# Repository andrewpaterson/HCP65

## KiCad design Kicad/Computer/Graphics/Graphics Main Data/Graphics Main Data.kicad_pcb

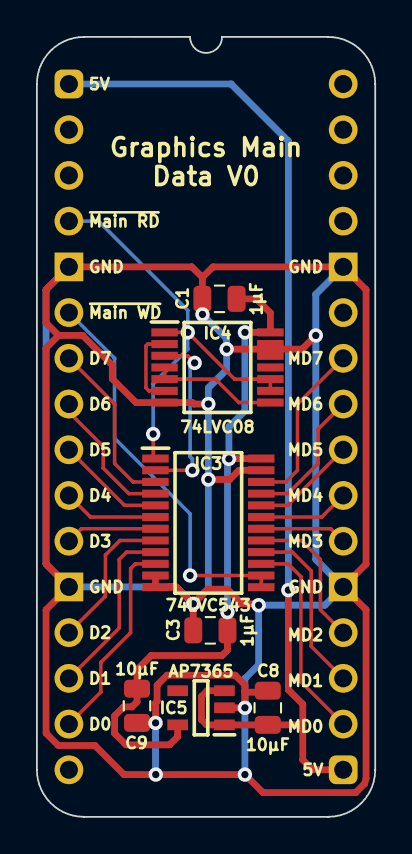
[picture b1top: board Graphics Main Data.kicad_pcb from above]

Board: 2 copper layers, 18.8 x 43.3 mm, 8 parts (0 on the bottom side), 24 nets.

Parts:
C1, C3: 1μF; C_0805
C8, C9: 10µF; C_0805
IC3: SN74LVC543APWR; SOP65P640X120-24N
IC4: 74LVC08APW,112; SOP65P640X110-14N
IC5: AP7365-33WG-7; SOT95P285X130-5N
J5: Board 2x16 W15.24mm; DIP-32_Board_W15.24mm

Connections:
5V: C8.1, IC5.1 (6VIn), IC5.3 (EN), J5.1, J5.17
/3.3V: C1.1, C3.1, C9.1, IC3.24 (3V), IC4.14 (3V), IC5.5 (3.3VOut)
/~Read_{2}: IC4.4 (2A), IC4.5 (2B), IC4.8 (3Y)
/~Read_{3}: IC4.2 (1B), IC4.6 (2Y)
/~Read_{4}: IC3.2 (~OEA), IC4.3 (1Y)
D0: IC3.10 (A8), J5.15
D1: IC3.9 (A7), J5.14
D2: IC3.8 (A6), J5.13
D3: IC3.7 (A5), J5.11
D4: IC3.6 (A4), J5.10
D5: IC3.5 (A3), J5.9
D6: IC3.4 (A2), J5.8
D7: IC3.3 (A1), J5.7
GND: C1.2, C3.2, C8.2, C9.2, IC3.11 (~CEAB), IC3.12 (GND), IC3.23 (~CEBA), IC4.7 (GND), IC4.12 (4A), IC4.13 (4B), IC5.2 (GND), J5.5, J5.12, J5.21, J5.28
MD0: IC3.15 (B8), J5.18
MD1: IC3.16 (B7), J5.19
MD2: IC3.17 (B6), J5.20
MD3: IC3.18 (B5), J5.22
MD4: IC3.19 (B4), J5.23
MD5: IC3.20 (B3), J5.24
MD6: IC3.21 (B2), J5.25
MD7: IC3.22 (B1), J5.26
~Main Read: IC3.1 (~LEB), IC4.1 (1A), IC4.9 (3A), IC4.10 (3B), J5.4
~Main Write: IC3.13 (~OEB), IC3.14 (~LEA), J5.6

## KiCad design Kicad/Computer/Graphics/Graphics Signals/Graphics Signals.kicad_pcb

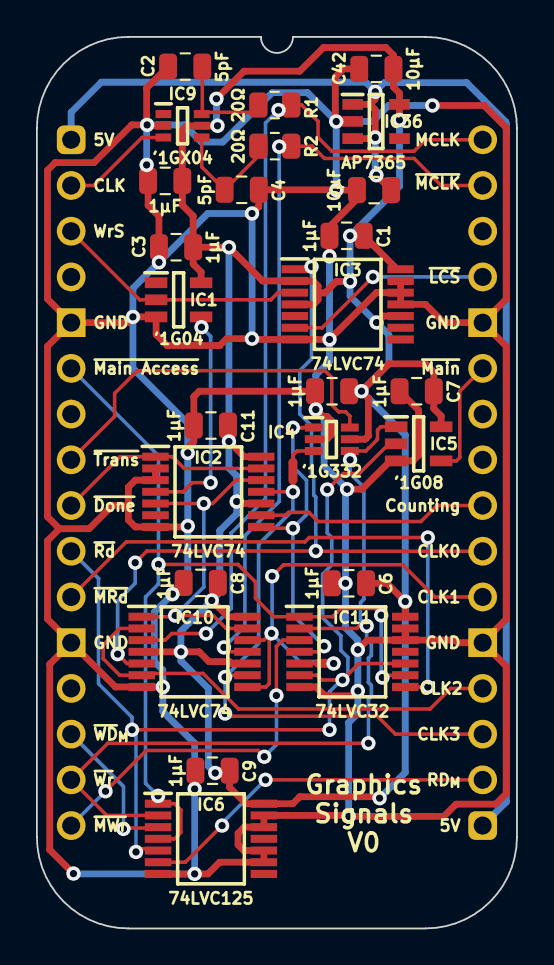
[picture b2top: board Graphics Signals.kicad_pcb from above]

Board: 2 copper layers, 26.7 x 49.5 mm, 28 parts (0 on the bottom side), 30 nets.

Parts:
C1, C3, C5, C6, C7, C8, C9, C10, C11: 1μF; C_0805
C2, C4: 5pF; C_0805
C41, C42: 10μF; C_0805
IC1: 74LVC1G04GV,125; SOT95P275X110-5N
IC2, IC3, IC10: 74LVC74APW,118; SOP65P640X110-14N
IC4: SN74LVC1G332DCKR; SOT65P210X110-6N
IC5: 74LVC1G08GV,125; SOT95P275X110-5N
IC6: 74LVC125APW-Q100J; SOP65P640X110-14N
IC9: 74LVC1GX04GW,125; SOP65P210X110-6N
IC11: 74LVC32APW,118; SOP65P640X110-14N
IC36: AP7365-33WG-7; SOT95P285X130-5N
J7: Board 2x16 W22.86mm; DIP-32_Board_W22.86mm
NT1, NT2: NetTie_2; NetTie-2_SMD_Pad0.5mm
R1, R2: 20Ω; R_0805

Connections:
5V: C41.1, IC36.1 (6VIn), IC36.3 (EN), J7.1, J7.17
/3.3V: C1.2, C3.1, C5.2, C6.2, C7.2, C8.2, C9.2, C10.2, C11.2, C42.1, IC1.5 (3V), IC2.10 (~2SD), IC2.14 (3V), IC3.2 (1D), IC3.4 (~1SD), IC3.10 (~2SD), IC3.14 (3V), IC4.5 (3V), IC5.5 (3V), IC6.14 (3V), IC9.5 (3V), IC10.4 (~1SD), IC10.10 (~2SD), IC10.14 (3V), IC11.14 (3V), IC36.5 (3.3VOut)
/Running: IC2.5 (1Q), IC2.12 (2D), IC10.1 (~1RD), IC10.13 (~2RD)
/~Counting: IC2.8 (~2Q), IC4.1 (A), IC11.4 (2A)
/~Write Start: IC1.4 (Y), IC2.4 (~1SD)
/~Write w/o Tansparency: IC4.3 (B), NT1.2
CLK0: IC3.1 (~1RD), IC10.5 (1Q), J7.23
CLK1: IC10.8 (~2Q), IC10.12 (2D), J7.22, NT2.1
CLK2: IC10.2 (1D), IC10.6 (~1Q), J7.20
CLK3: IC2.11 (2CP), IC10.9 (2Q), J7.19, NT1.1
Counting: IC2.9 (2Q), J7.24
GND: C1.1, C2.2, C3.2, C4.2, C5.1, C6.1, C7.1, C8.1, C9.1, C10.1, C11.1, C41.2, C42.2, IC1.3 (GND), IC2.2 (1D), IC2.3 (1CP), IC2.7 (GND), IC3.7 (GND), IC3.11 (2CP), IC3.12 (2D), IC3.13 (~2RD), IC4.2 (GND), IC5.3 (GND), IC6.7 (GND), IC6.9 (3A), IC6.10 (~3OE), IC6.12 (4A), IC6.13 (~4OE), IC9.2 (GND), IC10.7 (GND), IC11.7 (GND), IC11.12 (4A), IC11.13 (4B), IC36.2 (GND), J7.5, J7.12, J7.21, J7.28
MCLK: IC10.3 (1CP), J7.32, R1.2
Main CLK: IC9.3 (X1), J7.2
unnamed: C2.1, IC9.6 (Y), R1.1
unnamed: C4.1, IC9.4 (~Y), R2.1
unnamed: IC11.5 (2B), NT2.2
Transparent: IC4.6 (C), J7.8
Write Start: IC1.2 (A), IC3.3 (1CP), J7.3
~Done: IC2.1 (~1RD), IC2.13 (~2RD), J7.9
~Load Count Start: IC3.6 (~1Q), J7.29
~MCLK: IC10.11 (2CP), J7.31, R2.2
~Main Access: IC6.1 (~1OE), IC6.4 (~2OE), IC11.1 (1A), IC11.9 (3A), J7.6
~Main RD: IC6.6 (2Y), J7.18
~Main Read: IC11.8 (3Y), J7.11
~Main WD: IC6.3 (1Y), J7.14
~Main Write: IC11.3 (1Y), J7.16
~Main: IC5.4 (Y), J7.27
~Read: IC5.2 (A), IC6.5 (2A), IC11.6 (2Y), IC11.10 (3B), J7.10
~Write: IC4.4 (Y), IC5.1 (B), IC6.2 (1A), IC11.2 (1B), J7.15

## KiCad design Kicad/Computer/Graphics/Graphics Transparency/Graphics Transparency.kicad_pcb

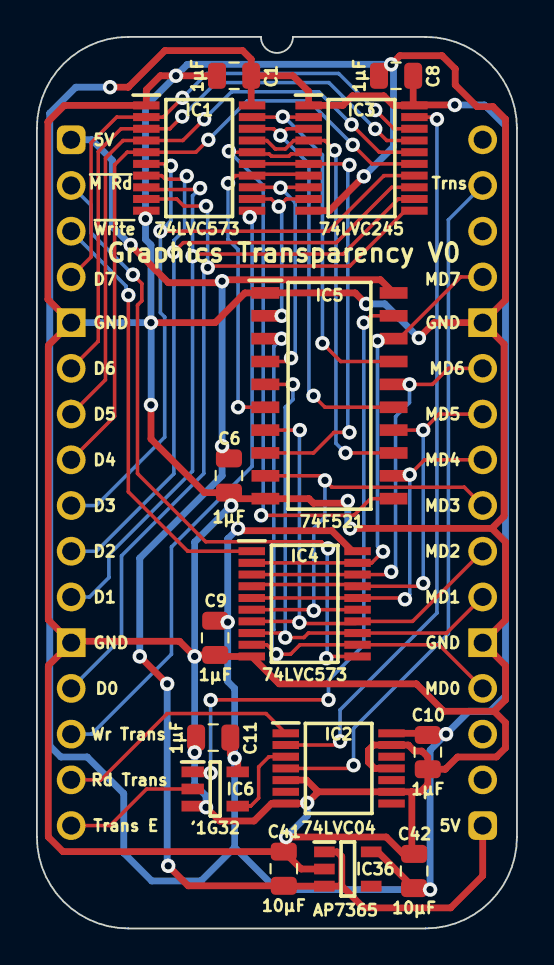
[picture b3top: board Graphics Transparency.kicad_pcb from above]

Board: 2 copper layers, 26.7 x 49.5 mm, 16 parts (0 on the bottom side), 36 nets.

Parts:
C1, C6, C8, C9, C10, C11: 1μF; C_0805
C41, C42: 10μF; C_0805
IC1, IC4: 74LVC573APW,118; SOP65P640X110-20N
IC2: 74LVC04APW,118; SOP65P640X110-14N
IC3: 74LVC245AT20; SOP65P640X120-20N
IC5: SN74F521NSR; SOIC127P780X200-20N
IC6: 74LVC1G32GV,125; SOT95P275X110-5N
IC36: AP7365-33WG-7; SOT95P285X130-5N
J7: Board 2x16 W22.86mm; DIP-32_Board_W22.86mm

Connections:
5V: C6.2, C41.1, IC5.20 (5V), IC36.1 (6VIn), IC36.3 (EN), J7.1, J7.17
/3.3V: C1.2, C8.2, C9.2, C10.2, C11.2, C42.1, IC1.20 (3V), IC2.14 (3V), IC3.1 (DIR), IC3.20 (3V), IC4.20 (3V), IC6.5 (3V), IC36.5 (3.3VOut)
/T0: IC1.12 (Q7), IC3.9 (A7), IC5.2 (P0)
/T1: IC1.13 (Q6), IC3.8 (A6), IC5.4 (P1)
/T2: IC1.14 (Q5), IC3.7 (A5), IC5.6 (P2)
/T3: IC1.15 (Q4), IC3.6 (A4), IC5.8 (P3)
/T4: IC1.16 (Q3), IC3.5 (A3), IC5.11 (P4)
/T5: IC1.17 (Q2), IC3.4 (A2), IC5.13 (P5)
/T6: IC1.18 (Q1), IC3.3 (A1), IC5.15 (P6)
/T7: IC1.19 (Q0), IC3.2 (A0), IC5.17 (P7)
/~Read Transparent Colour: IC2.2 (1Y), IC3.19 (~OE)
/~Transparent: IC2.3 (2A), IC6.4 (Y)
D0: IC1.9 (D7), IC3.11 (B7), J7.13
D1: IC1.8 (D6), IC3.12 (B6), J7.11
D2: IC1.7 (D5), IC3.13 (B5), J7.10
D3: IC1.6 (D4), IC3.14 (B4), J7.9
D4: IC1.5 (D3), IC3.15 (B3), J7.8
D5: IC1.4 (D2), IC3.16 (B2), J7.7
D6: IC1.3 (D1), IC3.17 (B1), J7.6
D7: IC1.2 (D0), IC3.18 (B0), J7.4
GND: C1.1, C6.1, C8.1, C9.1, C10.1, C11.1, C41.2, C42.2, IC1.1 (~OE), IC1.10 (GND), IC2.5 (3A), IC2.7 (GND), IC2.9 (4A), IC2.11 (5A), IC2.13 (6A), IC3.10 (GND), IC4.10 (GND), IC5.1 (~OE), IC5.10 (GND), IC6.3 (GND), IC36.2 (GND), J7.5, J7.12, J7.21, J7.28
MD0: IC4.9 (D7), IC4.12 (Q7), IC5.3 (Q0), J7.20
MD1: IC4.8 (D6), IC4.13 (Q6), IC5.5 (Q1), J7.22
MD2: IC4.7 (D5), IC4.14 (Q5), IC5.7 (Q2), J7.23
MD3: IC4.6 (D4), IC4.15 (Q4), IC5.9 (Q3), J7.24
MD4: IC4.5 (D3), IC4.16 (Q3), IC5.12 (Q4), J7.25
MD5: IC4.4 (D2), IC4.17 (Q2), IC5.14 (Q5), J7.26
MD6: IC4.3 (D1), IC4.18 (Q1), IC5.16 (Q6), J7.27
MD7: IC4.2 (D0), IC4.19 (Q0), IC5.18 (Q7), J7.29
unnamed: IC5.19 (~P=Q), IC6.1 (B)
Read Transparent Colour: IC2.1 (1A), J7.15
Transparency Enable: IC6.2 (A), J7.16
Transparent: IC2.4 (2Y), J7.31
Write Transparent Colour: IC1.11 (LE), J7.14
~Main Read: IC4.11 (LE), J7.2
~Write: IC4.1 (~OE), J7.3

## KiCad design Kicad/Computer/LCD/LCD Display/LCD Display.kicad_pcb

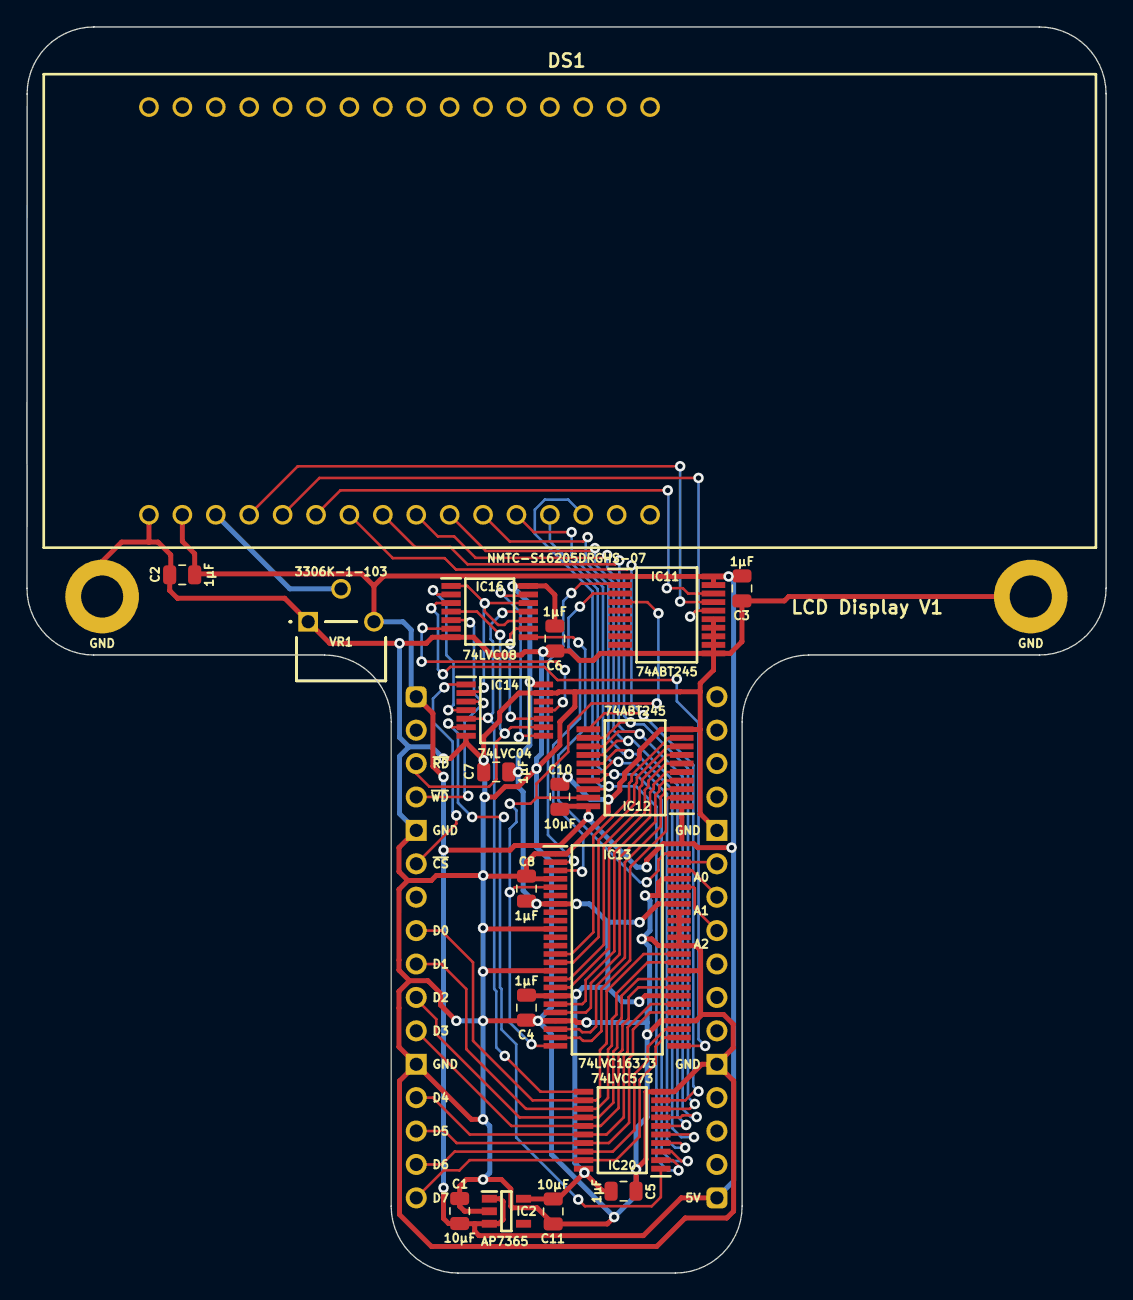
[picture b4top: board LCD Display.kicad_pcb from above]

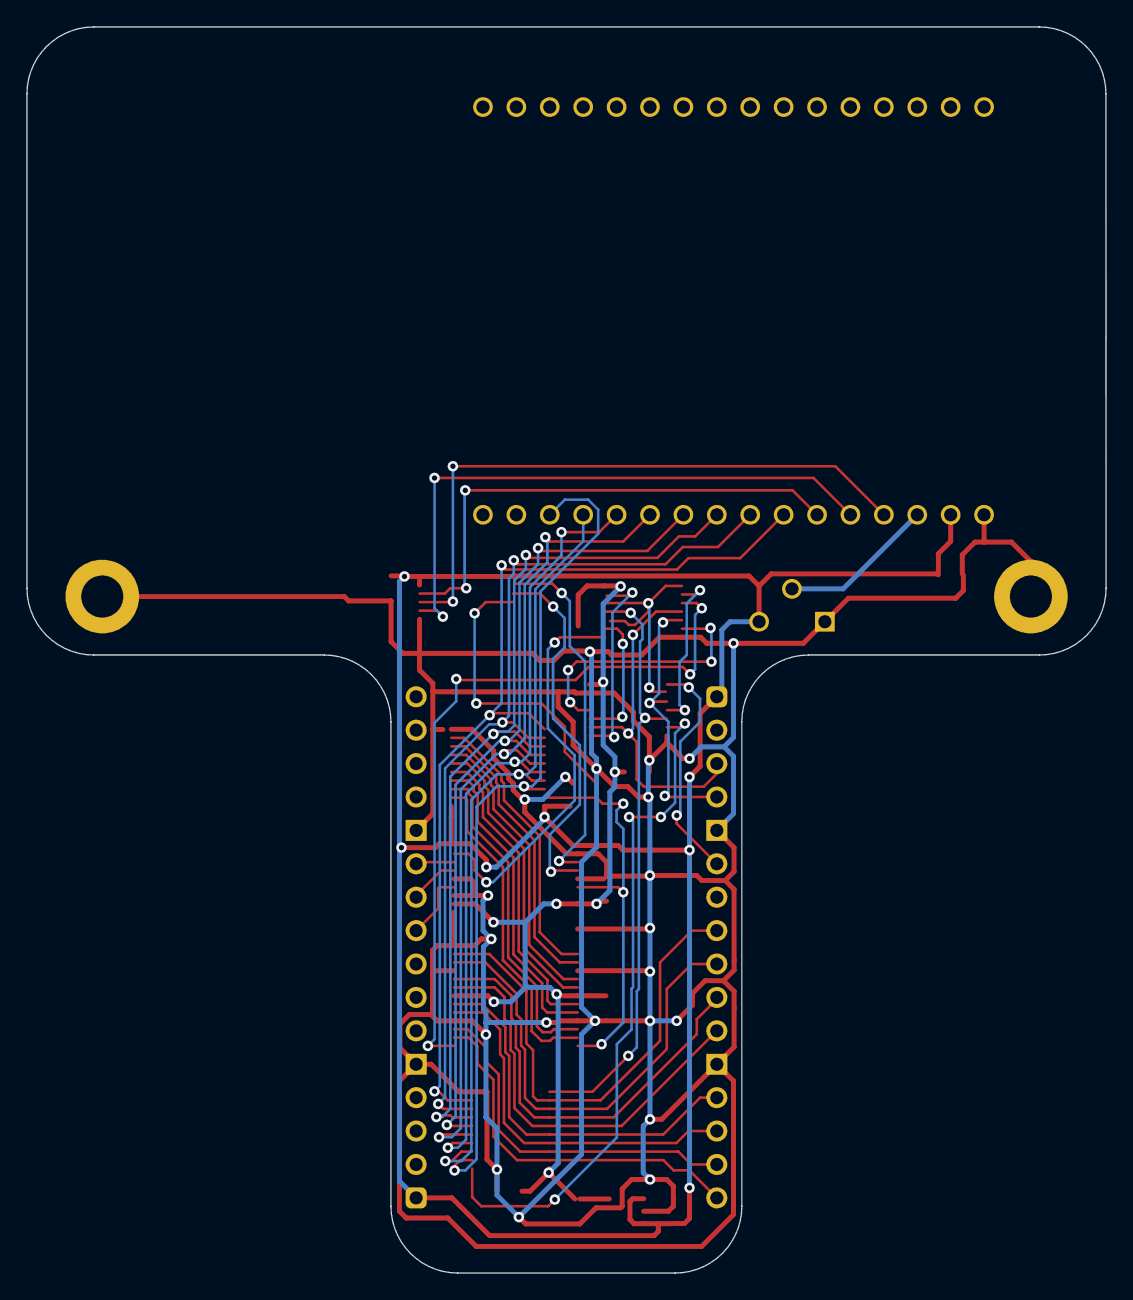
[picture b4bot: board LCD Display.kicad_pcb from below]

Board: 2 copper layers, 82.0 x 94.7 mm, 24 parts (2 on the bottom side), 49 nets.

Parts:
C1, C10, C11: 10μF; C_0805
C2, C3, C4, C5, C6, C7, C8: 1μF; C_0805
DS1: NMTC-S16205DRGHS-07; NMTCS16205DRGHS07_1
H1, H2: MountingHole_Pad; HCP65_MountingHole_M3_
IC2: AP7365-33WG-7; SOT95P285X130-5N
IC11, IC12: SN74ABT245BDBR; SOP65P780X200-20N
IC13: 74LVC16373ADL,118; SOP64P1025X280-48N
IC14: 74LVC04APW,118; SOP65P640X110-14N
IC16: 74LVC08APW,112; SOP65P640X110-14N
IC20: 74LVC573APW,118; SOP65P640X110-20N
J1: Board 2x16 W22.86mm; DIP-32_Board_W22.86mm_Nak
J2, J3: Pin_Header_01x16; PinHeader_1x16_P2.54mm_Vertical
VR1: 3306K-1-103; 3306K1103

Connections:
5V: C1.1, C2.1, C3.1, C10.1, DS1.2 (5V), IC2.1 (6VIn), IC2.3 (EN), IC11.1 (DIR), IC11.19 (~OE), IC11.20 (5V), IC12.1 (DIR), IC12.20 (5V), J1.1, J1.17, VR1.3 (VIN)
/3.3V: C4.1, C5.1, C6.1, C7.1, C8.1, C11.1, IC2.5 (3.3VOut), IC13.7 (3V), IC13.18 (3V), IC13.31 (3V), IC13.42 (3V), IC14.14 (3V), IC16.14 (3V), IC20.20 (3V)
/(RD+WD)·CS: IC13.48 (1LE), IC16.8 (3Y)
/CS: IC14.2 (1Y), IC16.1 (1A), IC16.10 (3B), IC16.12 (4A)
/D0_{Latch}: IC12.9 (A7), IC13.13 (2Q0)
/D1_{Latch}: IC12.8 (A6), IC13.14 (2Q1)
/D2_{Latch}: IC12.7 (A5), IC13.16 (2Q2)
/D3_{Latch}: IC12.6 (A4), IC13.17 (2Q3)
/D4_{Latch}: IC12.5 (A3), IC13.19 (2Q4)
/D5_{Latch}: IC12.4 (A2), IC13.20 (2Q5)
/D6_{Latch}: IC12.3 (A1), IC13.22 (2Q6)
/D7_{Latch}: IC12.2 (A0), IC13.23 (2Q7)
/DB0: DS1.7 (DB0), IC12.11 (B7), IC20.9 (D7)
/DB1: DS1.8 (DB1), IC12.12 (B6), IC20.8 (D6)
/DB2: DS1.9 (DB2), IC12.13 (B5), IC20.7 (D5)
/DB3: DS1.10 (DB3), IC12.14 (B4), IC20.6 (D4)
/DB4: DS1.11 (DB4), IC12.15 (B3), IC20.5 (D3)
/DB5: DS1.12 (DB5), IC12.16 (B2), IC20.4 (D2)
/DB6: DS1.13 (DB6), IC12.17 (B1), IC20.3 (D1)
/DB7: DS1.14 (DB7), IC12.18 (B0), IC20.2 (D0)
/E: DS1.6 (E), IC11.18 (B0)
/E_{Latch}: IC11.2 (A0), IC13.2 (1Q0)
/RD: IC14.8 (4Y), IC16.13 (4B)
/RD+WD: IC14.10 (5Y), IC16.9 (3A)
/RD·CS: IC14.5 (3A), IC16.11 (4Y), IC20.11 (LE)
/RS: DS1.4 (RS), IC11.17 (B1)
/RS_{Latch}: IC11.3 (A1), IC13.3 (1Q1)
/R~W: DS1.5 (R/~W), IC11.16 (B2)
/R~W_{Latch}: IC11.4 (A2), IC12.19 (~OE), IC13.5 (1Q2), IC13.24 (2~OE)
/V_{0}: DS1.3 (V_{O}), VR1.2 (VOUT)
/WD: IC14.4 (2Y), IC16.2 (1B)
/WD·CS: IC13.25 (2LE), IC16.3 (1Y)
/~RD+~CS: IC14.6 (3Y), IC20.1 (~OE)
/~RD·~WD: IC14.11 (5A), IC16.6 (2Y)
A0: IC13.47 (1D0), J1.27
A1: IC13.46 (1D1), J1.26
A2: IC13.44 (1D2), J1.25
D0: IC13.36 (2D0), IC20.12 (Q7), J1.8
D1: IC13.35 (2D1), IC20.13 (Q6), J1.9
D2: IC13.33 (2D2), IC20.14 (Q5), J1.10
D3: IC13.32 (2D3), IC20.15 (Q4), J1.11
D4: IC13.30 (2D4), IC20.16 (Q3), J1.13
D5: IC13.29 (2D5), IC20.17 (Q2), J1.14
D6: IC13.27 (2D6), IC20.18 (Q1), J1.15
D7: IC13.26 (2D7), IC20.19 (Q0), J1.16
Device ~CS: IC14.1 (1A), J1.6
GND: C1.2, C2.2, C3.2, C4.2, C5.2, C6.2, C7.2, C8.2, C10.2, C11.2, DS1.1 (GND), H1.1 (GND), H2.1 (GND), IC2.2 (GND), IC11.10 (GND), IC11.11 (B7), IC11.12 (B6), IC11.13 (B5), IC11.14 (B4), IC11.15 (B3), IC12.10 (GND), IC13.1 (1~OE), IC13.4 (GND), IC13.10 (GND), IC13.15 (GND), IC13.21 (GND), IC13.28 (GND), IC13.34 (GND), IC13.37 (1D7), IC13.38 (1D6), IC13.39 (GND), IC13.40 (1D5), IC13.41 (1D4), IC13.43 (1D3), IC13.45 (GND), IC14.7 (GND), IC14.13 (6A), IC16.7 (GND), IC20.10 (GND), J1.5, J1.12, J1.21, J1.28, VR1.1 (GND)
~RD: IC14.9 (4A), IC16.4 (2A), J1.3
~WD: IC14.3 (2A), IC16.5 (2B), J1.4

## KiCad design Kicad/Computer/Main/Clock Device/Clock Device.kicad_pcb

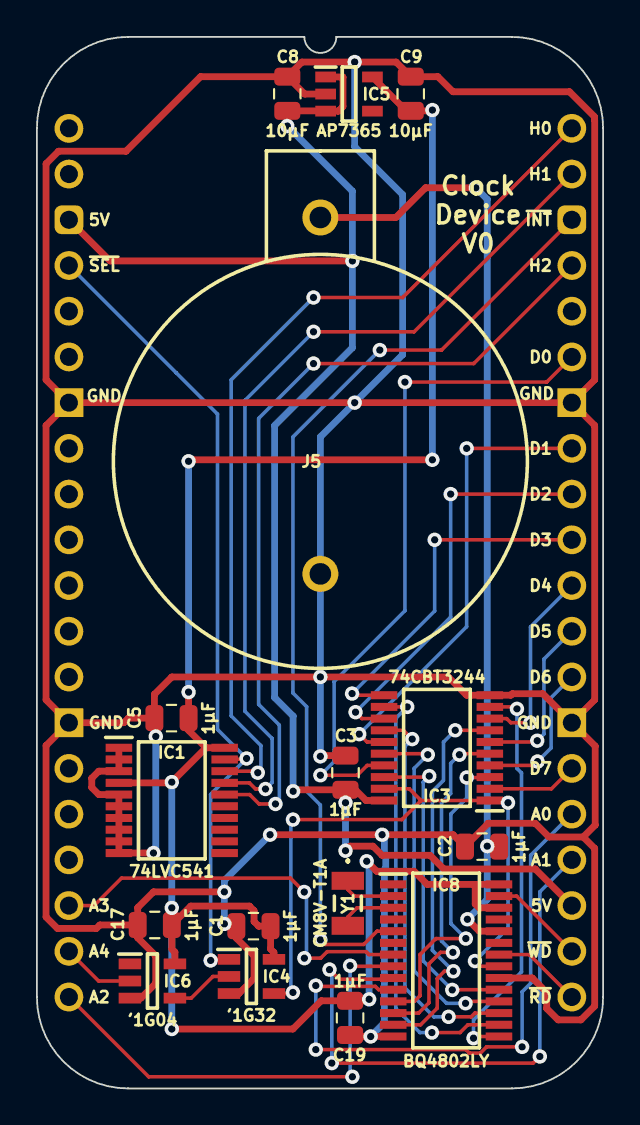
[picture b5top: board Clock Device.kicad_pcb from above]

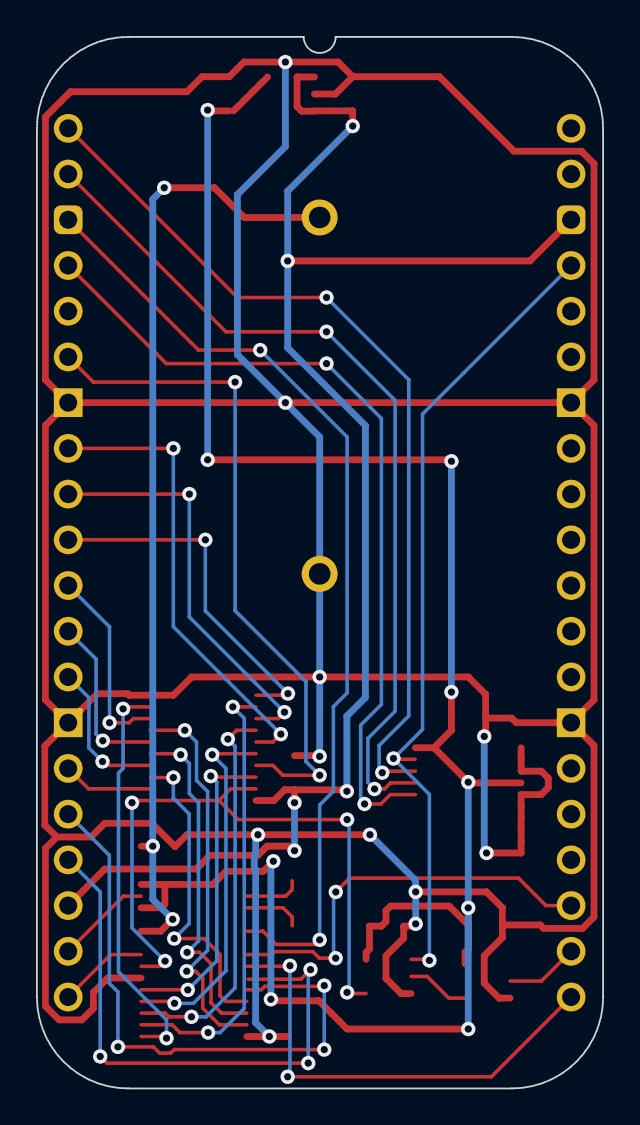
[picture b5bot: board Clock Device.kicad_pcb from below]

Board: 2 copper layers, 31.5 x 58.4 mm, 20 parts (2 on the bottom side), 36 nets.

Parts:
C1, C2, C3, C5, C17, C19: 1μF; C_0805
C8, C9: 10µF; C_0805
IC1: 74LVC541APW,118; SOP65P640X110-20N
IC3: SN74CBT3244CPWR; SOP65P640X120-20N
IC4: 74LVC1G32GV,125; SOT95P275X110-5N
IC5: AP7365-33WG-7; SOT95P285X130-5N
IC6: 74LVC1G04GV,125; SOT95P275X110-5N
IC8: BQ4802LYPWR; SOP65P640X120-28N
J1, J2: Conn_01x20; SIP_20_Pins
J3, J4: Pin_Header_01x20; PinHeader_1x20_P2.54mm_Vertical
J5: 237-8270
Y1: 32.768KHz; SC32S7PF20PPM

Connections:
5V: C3.1, C8.1, IC3.20 (5V), IC5.1 (6VIn), IC5.3 (EN), J1.3, J2.18
/3.3V: C1.1, C5.1, C9.1, C17.1, C19.1, IC1.4 (A2), IC1.20 (3V), IC4.5 (3V), IC5.5 (3.3VOut), IC6.5 (3V), IC8.26 (~CE_{IN}), IC8.28 (3V)
/3V Bat: C2.1, IC8.24 (BC), J5.1 (+)
/DQ0: IC3.3 (2B4), IC8.11 (DQ0)
/DQ1: IC3.5 (2B3), IC8.12 (DQ1)
/DQ2: IC3.7 (2B2), IC8.13 (DQ2)
/DQ3: IC3.9 (2B1), IC8.15 (DQ3)
/DQ4: IC3.12 (1B4), IC8.16 (DQ4)
/DQ5: IC3.14 (1B3), IC8.17 (DQ5)
/DQ6: IC3.16 (1B2), IC8.18 (DQ6)
/DQ7: IC3.18 (1B1), IC8.19 (DQ7)
/X1: IC8.2 (X1), Y1.1
/X2: IC8.3 (X2), Y1.2
/~A4: IC4.2 (A), IC6.4 (Y)
/~CS: IC3.1 (1~OE), IC3.19 (2~OE), IC4.4 (Y), IC8.21 (~CS)
A0: IC8.10 (A0), J2.16
A1: IC8.9 (A1), J2.17
A2: IC8.8 (A2), J1.20
A3: IC8.7 (A3), J1.18
A4: IC6.2 (A), J1.19
D0: IC3.17 (2A4), J2.6
D1: IC3.15 (2A3), J2.8
D2: IC3.13 (2A2), J2.9
D3: IC3.11 (2A1), J2.10
D4: IC3.8 (1A4), J2.11
D5: IC3.6 (1A3), J2.12
D6: IC3.4 (1A2), J2.13
D7: IC3.2 (1A1), J2.15
GND: C1.2, C2.2, C3.2, C5.2, C8.2, C9.2, C17.2, C19.2, IC1.1 (~OE1), IC1.2 (A0), IC1.3 (A1), IC1.5 (A3), IC1.6 (A4), IC1.7 (A5), IC1.8 (A6), IC1.9 (A7), IC1.10 (GND), IC3.10 (GND), IC4.3 (GND), IC5.2 (GND), IC6.3 (GND), IC8.14 (GND), IC8.20 (GND), J1.7, J1.14, J2.7, J2.14, J5.2 (-)
H0: IC1.18 (Y0), J2.1
H1: IC1.17 (Y1), J2.2
H2: IC1.16 (Y2), J2.4
~INT: IC8.5 (~INT), J2.3
~RD: IC8.22 (~OE), J2.20
~Select: IC1.19 (~OE2), IC4.1 (B), J1.4
~WD: IC8.27 (~WE), J2.19

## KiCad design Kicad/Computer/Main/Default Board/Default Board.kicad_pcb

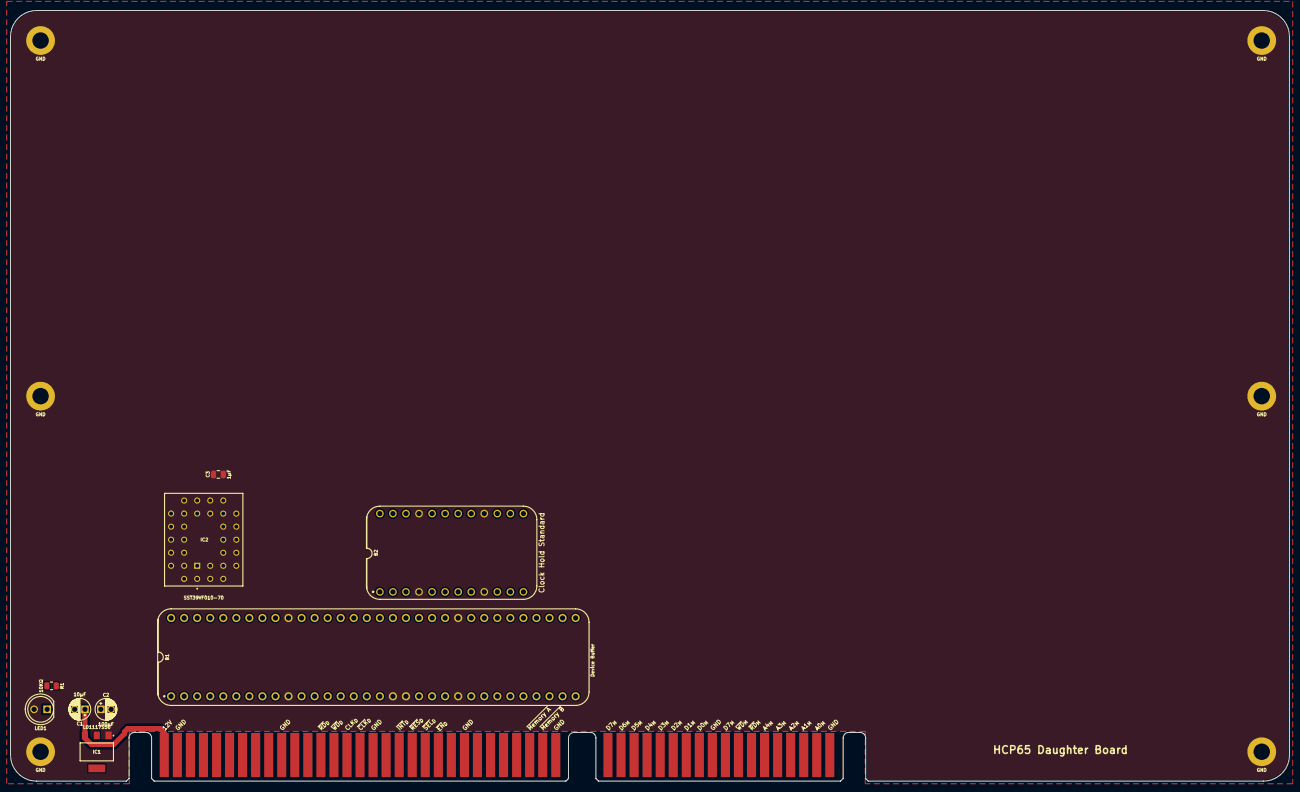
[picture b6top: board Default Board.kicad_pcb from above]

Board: 2 copper layers, 248.9 x 150.0 mm, 16 parts (0 on the bottom side), 66 nets.

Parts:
B1: Device Buffer; HCP65_Device_Buffer
B2: Clock Hold Standard; HCP65_Clock_Hold_Standard
C1: 10μF; CP_Radial_D4.0mm_P2.00mm
C2: 100μF; CP_Radial_D4.0mm_P2.00mm
C3: 1μF; C_0805
H1, H2, H8, H9, H16, H19: MountingHole_Pad; HCP65_MountingHole_M3_
IC1: LD1117S50C; LD1117S33C
IC2: SST39VF010-70-4I-NHE; 5408803224008
J5: 395-098-520-350; 98pin Edge Connector
LED1: Red; LED_D5.0mm
R1: 10KΩ; R_0805

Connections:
/3.3V: B2.6 (H2_{REG}), B2.7 (H1_{REG}), B2.8 (H0_{REG}), B2.24 (3.3V), C3.1, IC2.32 (3V)
/5V: B1.3 (5V), B1.35 (5V), B2.1 (5V), B2.13 (5V), C2.1, IC1.2 (5.0VOut), IC1.4 (5.0VOut), R1.2
/12V: C1.1, IC1.3 (15VIn), J5.B1
/A0: B1.64 (A0), IC2.12 (A0)
/A0_{D}: B1.1 (A0_{IN}), J5.A4
/A1: B1.63 (A1), IC2.11 (A1)
/A1_{D}: B1.2 (A1_{IN}), J5.A5
/A2: B1.62 (A2), IC2.10 (A2)
/A2_{D}: B1.4 (A2_{IN}), J5.A6
/A3: B1.61 (A3), IC2.9 (A3)
/A3_{D}: B1.5 (A3_{IN}), J5.A7
/A4: B1.60 (A4), IC2.8 (A4)
/A4_{D}: B1.6 (A4_{IN}), J5.A8
/A5: B1.59 (A5), IC2.7 (A5)
/A5_{D}: B1.7 (A5_{IN}), J5.A9
/A6: B1.58 (A6), IC2.6 (A6)
/A6_{D}: B1.8 (A6_{IN}), J5.A10
/A7: B1.57 (A7), IC2.5 (A7)
/A7_{D}: B1.9 (A7_{IN}), J5.A11
/A8: B1.56 (A8), IC2.27 (A8)
/A8_{D}: B1.11 (A8_{IN}), J5.A12
/A9: B1.54 (A9), IC2.26 (A9)
/A9_{D}: B1.12 (A9_{IN}), J5.A13
/A10: B1.53 (A10), IC2.23 (A10)
/A10_{D}: B1.13 (A10_{IN}), J5.A14
/A11: B1.52 (A11), IC2.25 (A11)
/A11_{D}: B1.14 (A11_{IN}), J5.A15
/A12: B1.51 (A12), IC2.4 (A12)
/A12_{D}: B1.15 (A12_{IN}), J5.A16
/A13: B1.50 (A13), IC2.28 (A13)
/A13_{D}: B1.16 (A13_{IN}), J5.A17
/A14: B1.49 (A14), IC2.29 (A14)
/A14_{D}: B1.17 (A14_{IN}), J5.A18
/A15: B1.48 (A15), IC2.3 (A15)
/A15_{D}: B1.18 (A15_{IN}), J5.A19
/A16: B1.47 (A16), IC2.2 (A16)
/A16_{D}: B1.19 (A16_{IN}), J5.A20
/CLK_{D}: B1.22 (S_{IN}), J5.B15
/D0: B1.34 (D0), IC2.13 (DQ0)
/D0_{D}: B1.31 (D0_{IN/OUT}), J5.A28
/D1: B1.36 (D1), IC2.14 (DQ1)
/D1_{D}: B1.30 (D1_{IN/OUT}), J5.A27
/D2: B1.37 (D2), IC2.15 (DQ2)
/D2_{D}: B1.29 (D2_{IN/OUT}), J5.A26
/D3: B1.38 (D3), IC2.17 (DQ3)
/D3_{D}: B1.28 (D3_{IN/OUT}), J5.A25
/D4: B1.39 (D4), IC2.18 (DQ4)
/D4_{D}: B1.27 (D4_{IN/OUT}), J5.A24
/D5: B1.40 (D5), IC2.19 (DQ5)
/D5_{D}: B1.26 (D5_{IN/OUT}), J5.A23
/D6: B1.41 (D6), IC2.20 (DQ6)
/D6_{D}: B1.25 (D6_{IN/OUT}), J5.A22
/D7: B1.43 (D7), IC2.21 (DQ7)
/D7_{D}: B1.24 (D7_{IN/OUT}), J5.A21
/GND: B1.10 (GND), B1.23 (GND), B1.42 (GND), B1.55 (GND), B2.4 (GND), B2.9 (GND), B2.16 (GND), B2.21 (GND), C1.2, C2.2, C3.2, H1.1 (GND), H2.1 (GND), H8.1 (GND), H9.1 (GND), H16.1 (GND), H19.1 (GND), IC1.1 (GND), IC2.16 (GND), J5.B2, J5.B10, J5.B17, J5.B24, J5.B31, J5.D9, J5.D18, LED1.2 (A)
/H0_{D}: B2.17 (H0_{OUT}), J5.A31
/H1_{D}: B2.18 (H1_{OUT}), J5.A30
/H2_{D}: B2.19 (H2_{OUT}), J5.A29
/~Device ROM: B2.5 (~Device_ROM), IC2.22 (~CE)
/~Device Select: B1.33 (Deivce_~CS), B2.11 (~Device_Select)
/~RD: B1.46 (~RD), B2.10 (~RD), IC2.24 (~OE)
/~RD_{D}: B1.20 (~RD_{IN}), J5.B13
/~Select_{D}: B1.32 (Deivce_~CS_{IN}), J5.B21
/~WD: B1.45 (~WD), B2.12 (~WD), IC2.31 (~WE)
/~WD_{D}: B1.21 (~WD_{IN}), J5.B14
unnamed: LED1.1 (K), R1.1

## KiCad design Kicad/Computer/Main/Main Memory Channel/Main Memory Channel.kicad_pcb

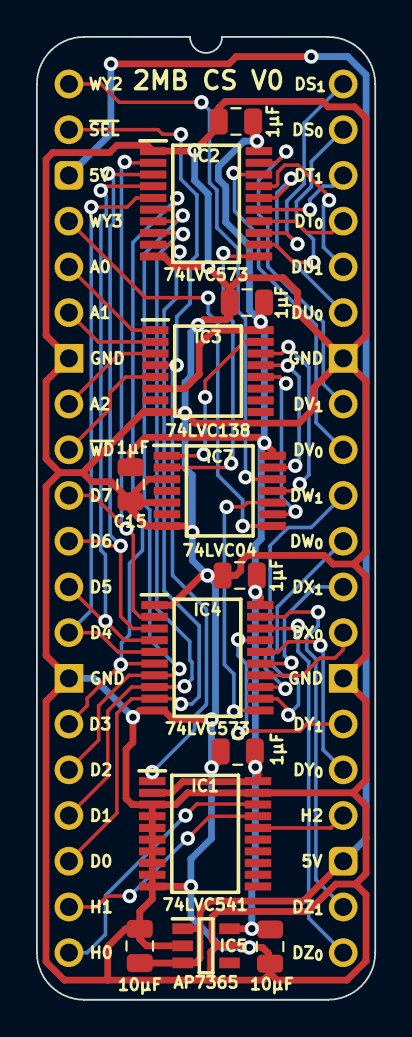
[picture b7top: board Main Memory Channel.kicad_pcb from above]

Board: 2 copper layers, 18.8 x 53.5 mm, 14 parts (0 on the bottom side), 43 nets.

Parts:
C5, C6, C7, C10, C15: 1μF; C_0805
C8, C9: 10µF; C_0805
IC1: 74LVC541APW,118; SOP65P640X110-20N
IC2, IC4: 74LVC573APW,118; SOP65P640X110-20N
IC3: 74LVC138APW-Q100J; SOP65P640X110-16N
IC5: AP7365-33WG-7; SOT95P285X130-5N
IC7: 74LVC04APW,118; SOP65P640X110-14N
J4: Board 2x20 W15.24mm; DIP-40_Board_W15.24mm

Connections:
5V: C8.1, IC5.1 (6VIn), IC5.3 (EN), J4.3, J4.23
/3.3V: C5.1, C6.1, C7.1, C9.1, C10.1, C15.1, IC1.2 (A0), IC1.20 (3V), IC2.20 (3V), IC3.6 (E3), IC3.16 (3V), IC4.20 (3V), IC5.5 (3.3VOut), IC7.14 (3V)
/WY_{0}: IC2.11 (LE), IC7.2 (1Y)
/WY_{1}: IC4.11 (LE), IC7.10 (5Y)
/~WY_{0}: IC3.15 (~Y0), IC7.1 (1A)
/~WY_{1}: IC3.14 (~Y1), IC7.11 (5A)
/~WY_{2}: IC3.13 (~Y2), IC7.13 (6A)
/~WY_{3}: IC3.12 (~Y3), IC7.9 (4A)
A0: IC3.1 (A0), J4.5
A1: IC3.2 (A1), J4.6
A2: IC3.3 (A2), J4.8
D0: IC2.9 (D7), IC4.9 (D7), J4.18
D1: IC2.8 (D6), IC4.8 (D6), J4.17
D2: IC2.7 (D5), IC4.7 (D5), J4.16
D3: IC2.6 (D4), IC4.6 (D4), J4.15
D4: IC2.5 (D3), IC4.5 (D3), J4.13
D5: IC2.4 (D2), IC4.4 (D2), J4.12
D6: IC2.3 (D1), IC4.3 (D1), J4.11
D7: IC2.2 (D0), IC4.2 (D0), J4.10
Device_{(S)} 2MB Select_{0}: IC2.12 (Q7), J4.39
Device_{(S)} 2MB Select_{1}: IC2.13 (Q6), J4.40
Device_{(T)} 2MB Select_{0}: IC2.14 (Q5), J4.37
Device_{(T)} 2MB Select_{1}: IC2.15 (Q4), J4.38
Device_{(U)} 2MB Select_{0}: IC2.16 (Q3), J4.35
Device_{(U)} 2MB Select_{1}: IC2.17 (Q2), J4.36
Device_{(V)} 2MB Select_{0}: IC2.18 (Q1), J4.32
Device_{(V)} 2MB Select_{1}: IC2.19 (Q0), J4.33
Device_{(W)} 2MB Select_{0}: IC4.12 (Q7), J4.30
Device_{(W)} 2MB Select_{1}: IC4.13 (Q6), J4.31
Device_{(X)} 2MB Select_{0}: IC4.14 (Q5), J4.28
Device_{(X)} 2MB Select_{1}: IC4.15 (Q4), J4.29
Device_{(Y)} 2MB Select_{0}: IC4.16 (Q3), J4.25
Device_{(Y)} 2MB Select_{1}: IC4.17 (Q2), J4.26
Device_{(Z)} 2MB Select_{0}: IC4.18 (Q1), J4.21
Device_{(Z)} 2MB Select_{1}: IC4.19 (Q0), J4.22
GND: C5.2, C6.2, C7.2, C8.2, C9.2, C10.2, C15.2, IC1.3 (A1), IC1.4 (A2), IC1.5 (A3), IC1.6 (A4), IC1.7 (A5), IC1.8 (A6), IC1.9 (A7), IC1.10 (GND), IC1.19 (~OE2), IC2.1 (~OE), IC2.10 (GND), IC3.8 (GND), IC4.1 (~OE), IC4.10 (GND), IC5.2 (GND), IC7.3 (2A), IC7.5 (3A), IC7.7 (GND), J4.7, J4.14, J4.27, J4.34
H0: IC1.18 (Y0), J4.20
H1: IC1.17 (Y1), J4.19
H2: IC1.16 (Y2), J4.24
WY_{2}: IC7.12 (6Y), J4.1
WY_{3}: IC7.8 (4Y), J4.4
~Select: IC1.1 (~OE1), IC3.4 (~E1), J4.2
~WD: IC3.5 (~E2), J4.9

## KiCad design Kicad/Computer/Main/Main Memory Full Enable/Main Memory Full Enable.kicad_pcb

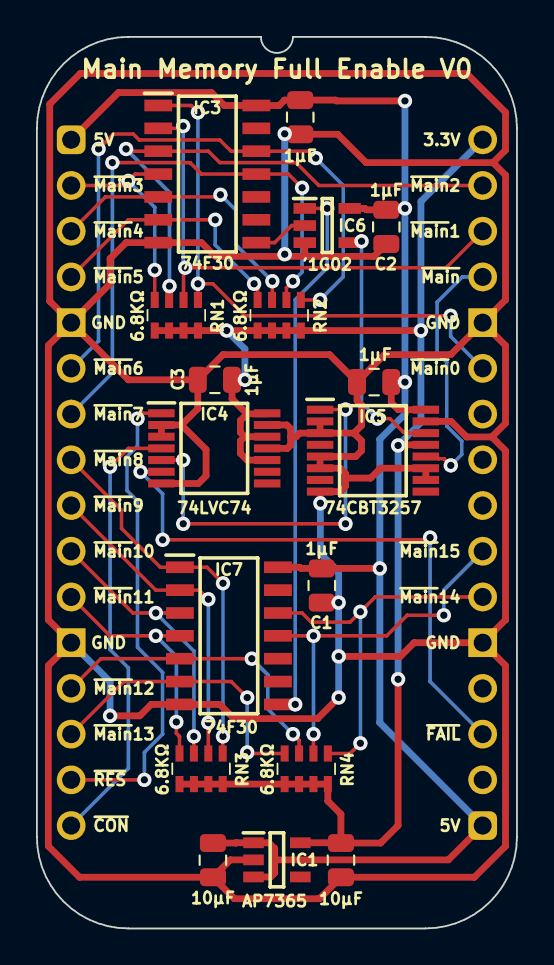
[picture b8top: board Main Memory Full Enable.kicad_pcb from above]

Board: 2 copper layers, 26.7 x 49.5 mm, 18 parts (0 on the bottom side), 27 nets.

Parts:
C1, C2, C3, C4, C6: 1μF; C_0805
C10, C11: 10µF; C_0805
IC1: AP7365-33WG-7; SOT95P285X130-5N
IC3, IC7: SN74F30DR; SOIC127P600X175-14N
IC4: 74LVC74APW,118; SOP65P640X110-14N
IC5: SN74CBT3257CPWR; SOP65P640X120-16N
IC6: 74LVC1G02GV,125; SOT95P275X110-5N
J2: Board 2x16 W22.86mm; DIP-32_Board_W22.86mm
RN1, RN2, RN3, RN4: CAY16-682J4LF; CAY16-J4

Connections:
3.3V: C3.1, C11.1, IC1.5 (3.3VOut), IC4.10 (~2SD), IC4.12 (2D), IC4.14 (3V), IC5.13 (4B2), J2.32, RN1.5 (R4), RN1.6 (R3), RN1.7 (R2), RN1.8 (R1), RN2.5 (R4), RN2.6 (R3), RN2.7 (R2), RN2.8 (R1), RN3.5 (R4), RN3.6 (R3), RN3.7 (R2), RN3.8 (R1), RN4.5 (R4), RN4.6 (R3), RN4.7 (R2), RN4.8 (R1)
5V: C1.1, C2.1, C4.1, C6.1, C10.1, IC1.1 (6VIn), IC1.3 (EN), IC3.14 (5V), IC5.16 (5V), IC6.5 (3V), IC7.14 (5V), J2.1, J2.17
/Contention: IC4.5 (1Q), IC5.1 (S)
/Pre-Main Memory A: IC3.8 (Y), IC6.2 (A)
/Pre-Main Memory B: IC6.1 (B), IC7.8 (Y)
/~Pre-Main Memory: IC5.14 (4B1), IC6.4 (Y)
GND: C1.2, C2.2, C3.2, C4.2, C6.2, C10.2, C11.2, IC1.2 (GND), IC3.7 (GND), IC4.2 (1D), IC4.3 (1CP), IC4.7 (GND), IC4.11 (2CP), IC4.13 (~2RD), IC5.2 (1B1), IC5.3 (1B2), IC5.5 (2B1), IC5.6 (2B2), IC5.8 (GND), IC5.10 (3B2), IC5.11 (3B1), IC5.15 (~OE), IC6.3 (GND), IC7.7 (GND), J2.5, J2.12, J2.21, J2.28
~Contention: IC4.6 (~1Q), J2.19
~Main Memory: IC5.12 (4A), J2.29
~Main0: IC3.1 (A), J2.27, RN1.1 (R1)
~Main1: IC3.2 (B), J2.30, RN1.2 (R2)
~Main2: IC3.3 (C), J2.31, RN1.3 (R3)
~Main3: IC3.4 (D), J2.2, RN1.4 (R4)
~Main4: IC3.5 (E), J2.3, RN2.3 (R3)
~Main5: IC3.6 (F), J2.4, RN2.4 (R4)
~Main6: IC3.12 (H), J2.6, RN2.1 (R1)
~Main7: IC3.11 (G), J2.7, RN2.2 (R2)
~Main8: IC7.1 (A), J2.8, RN3.1 (R1)
~Main9: IC7.2 (B), J2.9, RN3.2 (R2)
~Main10: IC7.3 (C), J2.10, RN3.3 (R3)
~Main11: IC7.4 (D), J2.11, RN3.4 (R4)
~Main12: IC7.5 (E), J2.13, RN4.3 (R3)
~Main13: IC7.6 (F), J2.14, RN4.4 (R4)
~Main14: IC7.12 (H), J2.22, RN4.1 (R1)
~Main15: IC7.11 (G), J2.23, RN4.2 (R2)
~Reset: IC4.1 (~1RD), J2.15
~Set Contention: IC4.4 (~1SD), J2.16
